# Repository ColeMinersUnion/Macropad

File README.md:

# Macropad
## Description

This macropad was built with a Raspberry Ri Rico using [CircuitPython.](https://circuitpython.org/) The code in this repository includes volume control and a Three pseudo-Clipboards. Shown below are instructions as well as files to edit or order PCBs. 

## Setup
### Thonny
Please install the latest version of thonny available at: [Thonny](https://thonny.org/). Thonny is a code editor that specializes in developing solutions for CircuitPython and MicroPython systems. 

### Supporting Documentation
For more information on the Mechanical Key breakout boards, as well as some of the code used in development: [Adafruit Tutorial](https://learn.adafruit.com/neokey-breakout/circuitpython-python) \
For more information on the Rotary Encoder, specifically as a volume knob: [Adafruit Tutorial](https://learn.adafruit.com/trinket-usb-volume-knob/add-a-mute-button) \

## Shopping List
This PCB uses four main components. A [raspberry Pi Pico](https://www.raspberrypi.com/products/raspberry-pi-pico/), five [Neokey socket breakout boards](https://www.adafruit.com/product/4978), one [rotary encoder](https://www.adafruit.com/product/377) and my custom circuit board. 

### Printed Circuit Board
The PCB files can be made from the KiCAD project found in the `PCB/` folder in this repository. 
[An Image of a printed circuit board](/media/CompletedPCB.JPG)

## Code
### Library Downloads
All of these libraries can be found on [pypi](https://pypi.org/)) for more information.\
Libraries To Download\
├── adafruit-circuitpython-neopixel\
└── adafruit-circuitpython-hid

### Import Statements
Import all of the necessary libraries. Most of which are included in the circuitpython interpreter.
```Python
#Basic Imports
import board
import time
import usb_hid

#For the Rotary Encoder
import digitalio
import rotaryio
from adafruit_hid.consumer_control import ConsumerControl
from adafruit_hid.consumer_control import ConsumerControlCode

#For the keys
import keypad
import neopixel
from adafruit_hid.keyboard import Keyboard
from adafruit_hid.keycode import Keycode
```

### Setting up the Encoder
This sets up all of the neccessary objects and variables for the encoder functionality. We use a button state variable to track mute state. 
```Python
#setting the mute button
button = digitalio.DigitalInOut(board.GP17)
button.direction = digitalio.Direction.INPUT
button.pull = digitalio.Pull.UP

encoder = rotaryio.IncrementalEncoder(board.GP14, board.GP15)
#setting up the keypoad and volume controls
cc = ConsumerControl(usb_hid.devices
#using the encoder button as a toggle
button_state = None
last_position = encoder.position
```

### Setting up the Keys
This section is meant to be general and just to show how the keys work before implementing layers or extra functionality. It does follow the previous physical prototype, notably that there are only 5 keys. 
```Python
#setting the brightness
#Any value from 0-1, the LEDs are very bright
BRIGHTNESS = 0.25

PIXEL_PIN = board.GP28
KEY_PINS = (board.GP27, board.GP26, board.GP22, board.GP21, board.GP20)
KEY_VALUE = (Keycode.A, Keycode.B, Keycode.C, Keycode.D, Keycode.E)
NUM_PIXELS = len(KEY_PINS)

#creating the neopixel obj
pixels = neopixel.NeoPixel(PIXEL_PIN, NUM_PIXELS, brightness=BRIGHTNESS)
#initial light up
for k in pixels:
    k = (0, 255, 0)

#creating a keypad obj
keys = keypad.Keys(KEY_PINS, value_when_pressed=False, pull=True)
time.sleep(1) #avoiding conflicts with OS
kboard = Keyboard(usb_hid.devices)
```

### Running Loop (Encoder)
Both sections of code in Running Loop should be wrapped in the SAME loop:
```Python
while(true):
```
This section details how the encoder runs to mute, decrement, or increment volume. 
```Python
    #This is my encoder code.
    #calculate change of position
    current_position = encoder.position
    position_change = current_position - last_position
    #logic for encoder.
    if position_change > 0:
        for _ in range(position_change):
            #changing volume
            cc.send(ConsumerControlCode.VOLUME_DECREMENT)
        print(current_position)
    elif position_change < 0:
        for _ in range(-position_change):
            cc.send(ConsumerControlCode.VOLUME_INCREMENT)
        print(current_position)
    last_position = current_position
    
    #muting. 
    if not button.value and button_state is None:
        button_state = "pressed"
    if button.value and button_state == "pressed":
        print("Button pressed.")
        cc.send(ConsumerControlCode.MUTE)
        button_state = None
```
### Running Loop (Keys)
Most of the heavy lifting for the keys was done during initialization. 
```Python
    #keyboard stuff
    event = keys.events.get()
    
    #initial push.
    if event and event.pressed:
        #which key did I press?
        key_index = event.key_number
        print(key_index)
        #on push
        pixels[key_index] = (0, 0, 255)
        kboard.press(KEY_VALUE[key_index])
        
    if event and event.released:
        pixels[event.key_number] =(0, 255, 0)
        kboard.release_all()
```

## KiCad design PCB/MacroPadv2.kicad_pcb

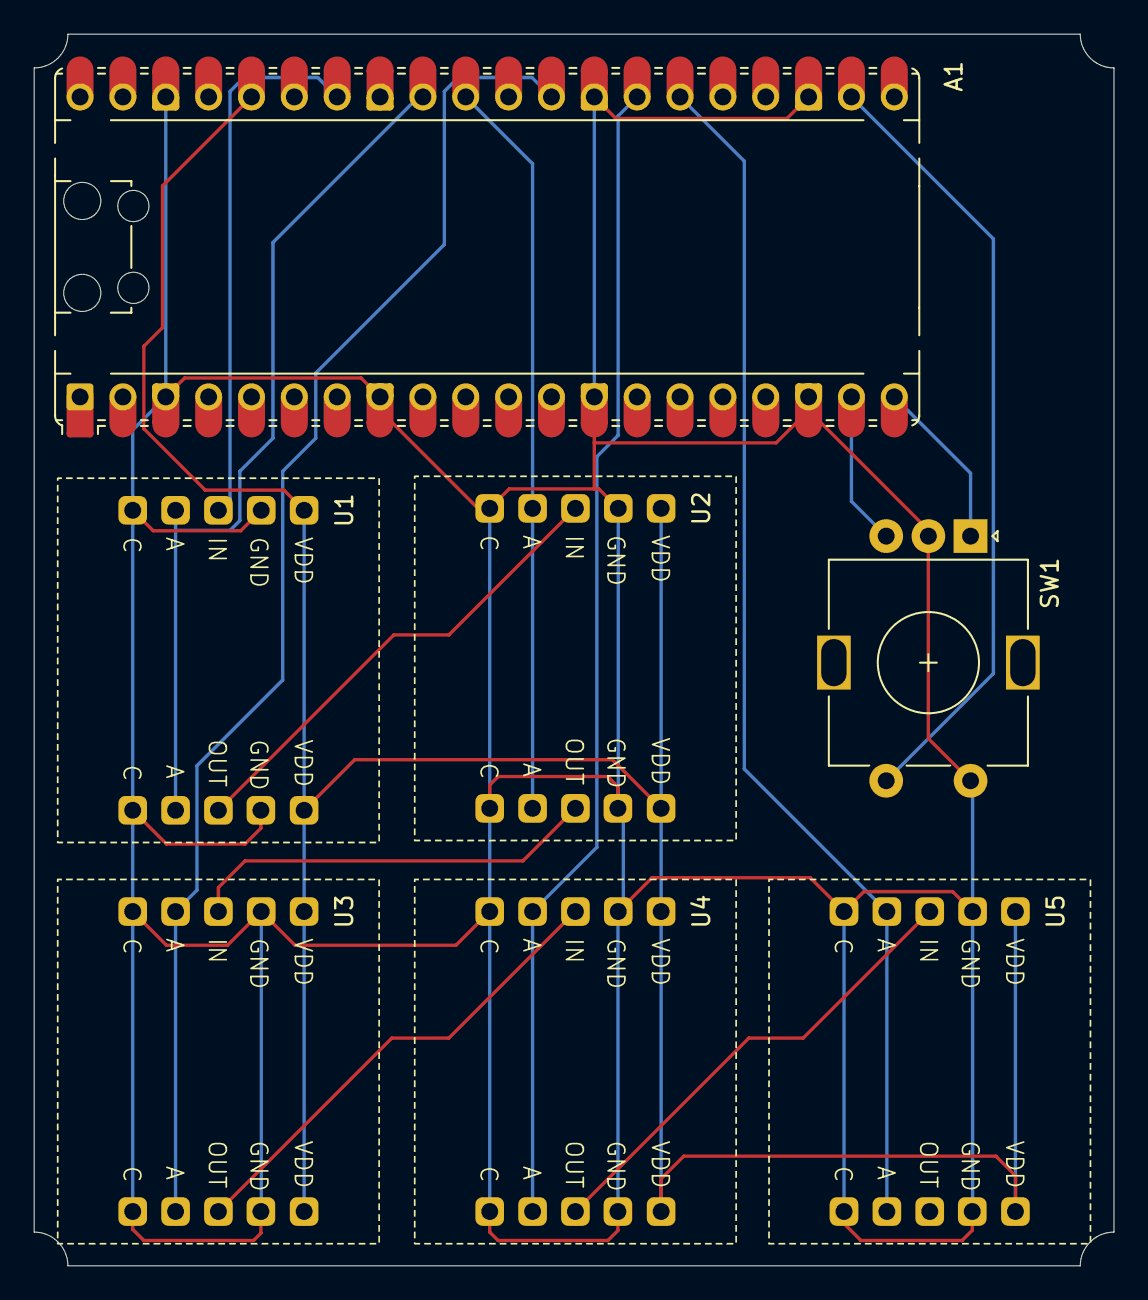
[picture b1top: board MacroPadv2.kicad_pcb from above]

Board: 2 copper layers, 64.0 x 73.0 mm, 7 parts (0 on the bottom side), 15 nets.

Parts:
A1: RaspberryPi_Pico; RaspberryPi_Pico_Common_Unspecified
SW1: RotaryEncoder_Switch; RotaryEncoder_Alps_EC11E-Switch_Vertical_H20mm
U1, U2, U3, U4, U5: Neokey_Custom_Footprint

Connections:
+3V3: A1.36 (3V3), U1.1 (VDD), U2.1 (VDD), U3.1 (VDD), U4.1 (VDD), U5.1 (VDD)
/A: A1.20 (GPIO15), SW1.A
/B: A1.19 (GPIO14), SW1.B
/SW: A1.22 (GPIO17), SW1.S1
/U1->U2: U1.4 (NEO_OUT), U2.3 (NEO_IN)
/U1_Anode: A1.32 (GPIO27_ADC1), U1.5 (SWITCHA)
/U1_IN: A1.34 (GPIO28_ADC2), U1.3 (NEO_IN)
/U2->U3: U2.4 (NEO_OUT), U3.3 (NEO_IN)
/U2_Anode: A1.31 (GPIO26_ADC0), U2.5 (SWITCHA)
/U3->U4: U3.4 (NEO_OUT), U4.3 (NEO_IN)
/U3_Anode: A1.29 (GPIO22), U3.5 (SWITCHA)
/U4->U5: U4.4 (NEO_OUT), U5.3 (NEO_IN)
/U4_Anode: A1.27 (GPIO21), U4.5 (SWITCHA)
/U5_Anode: A1.26 (GPIO20), U5.5 (SWITCHA)
GND: A1.3 (GND), A1.8 (GND), A1.13 (GND), A1.18 (GND), A1.23 (GND), A1.28 (GND), A1.38 (GND), SW1.C, SW1.S2, U1.2 (GND), U1.6 (SWITCHC), U2.2 (GND), U2.6 (SWITCHC), U3.2 (GND), U3.6 (SWITCHC), U4.2 (GND), U4.6 (SWITCHC), U5.2 (GND), U5.6 (SWITCHC)

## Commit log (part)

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2024-08-17 Create code.py
    Copying content from the macropad.
2024-08-17 Update README.md
    Initial progress. Starting some layout things and whatnot.
